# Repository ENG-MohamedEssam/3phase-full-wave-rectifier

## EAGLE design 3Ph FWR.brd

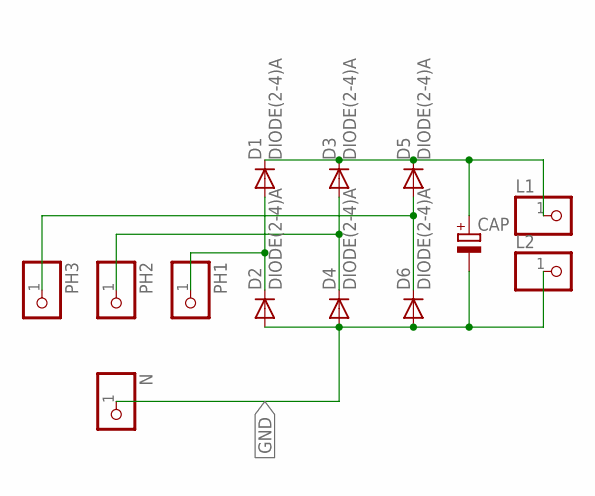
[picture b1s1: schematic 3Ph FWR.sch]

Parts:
CAP: CAP_POL; E3,5-8
D1, D2, D3, D4, D5, D6: DIODE(2-4)A; DO35-10
L1, L2: PINHD-1X1; 1X01
N: PINHD-1X1; 1X01
PH1, PH2, PH3: PINHD-1X1; 1X01

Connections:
GND: CAP.-, D2.A, D4.A, D6.A, L2.1, N.1
unnamed: D1.A, D2.C, PH1.1
unnamed: D3.A, D4.C, PH2.1
unnamed: D5.A, D6.C, PH3.1
unnamed: CAP.+, D1.C, D3.C, D5.C, L1.1

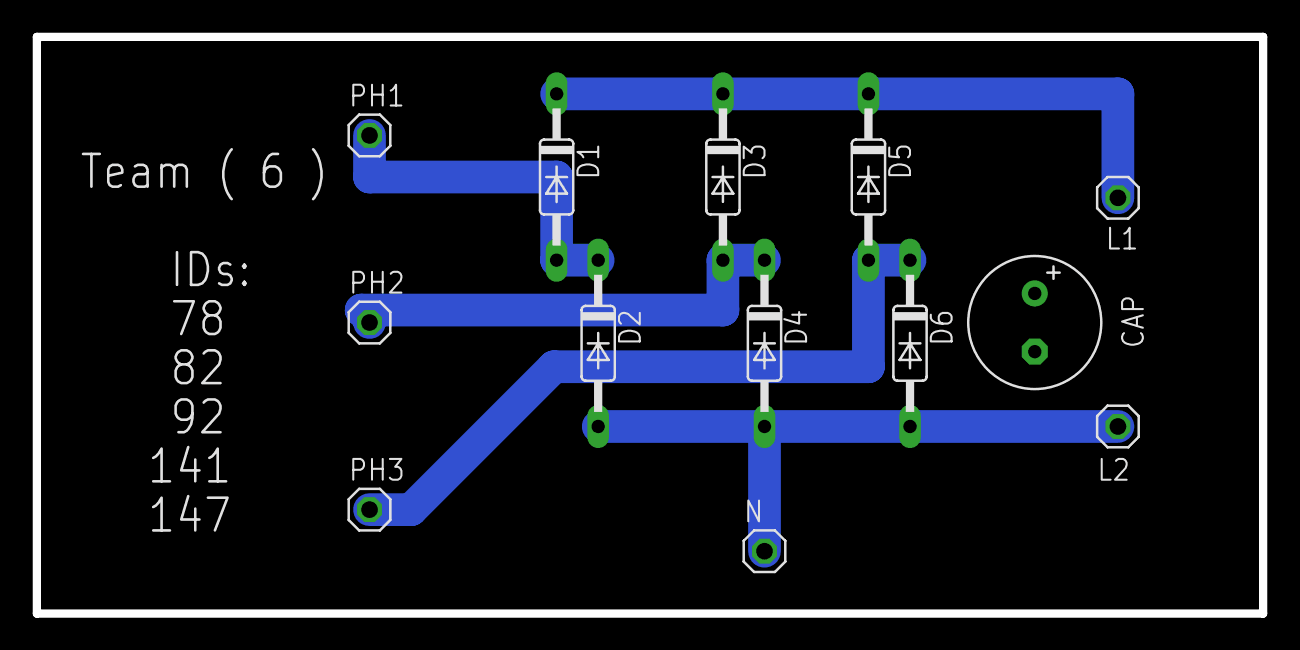
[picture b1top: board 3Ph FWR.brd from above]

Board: 2 copper layers, 74.9 x 35.2 mm, 13 parts (0 on the bottom side), 5 nets.
